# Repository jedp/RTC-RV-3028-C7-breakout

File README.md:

# RTC RV-3028-C7 Breakout Board

If you're using an Arduino, this goes nicely with Constantin Koch's
[RV-3038-C7-Arduino_Library](https://github.com/constiko/RV-3028_C7-Arduino_Library/),
which you can download direcly from the Arduino Library Manager.

Dimensions: 18.8mm x 22.6mm.

## BOM

- U1: RV-3028-C7 RTC
- C1: 0.1µ 0603
- C2: 0.1µ 0603
- R1: 10k 0603 (*Do Not Populate*; see datasheet for details.)
- R2: 10k 0603
- R3: 1k 0603
- R4: 10k 0603
- R5: 10k 0603
- R6: 10k 0603
- BT1: MS621F battery
- J1: Conn 1x4 female, 2.54mm
- J2: Conn 1x4 female, 2.54mm

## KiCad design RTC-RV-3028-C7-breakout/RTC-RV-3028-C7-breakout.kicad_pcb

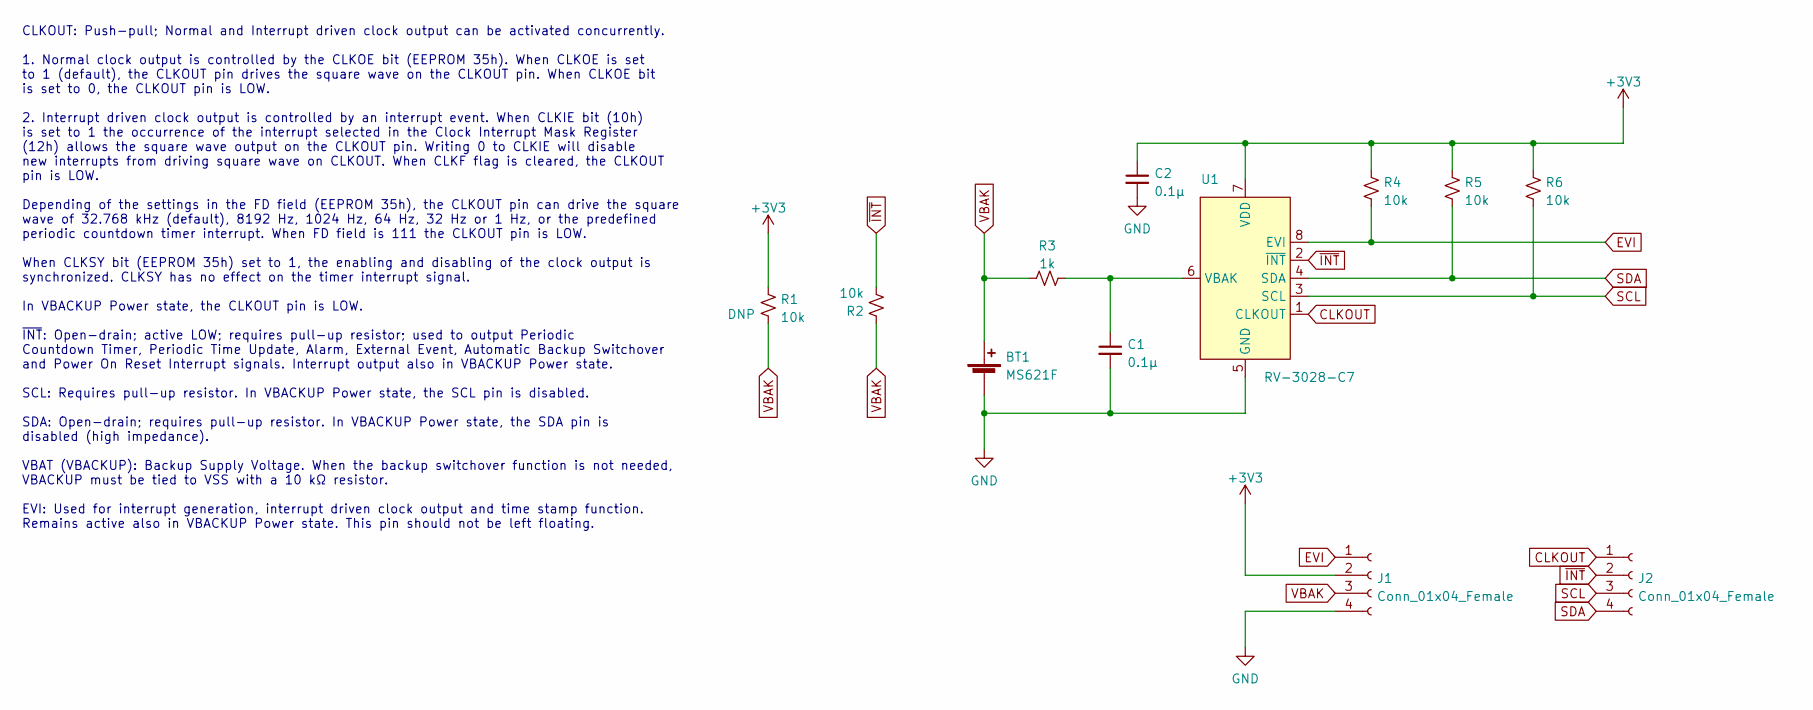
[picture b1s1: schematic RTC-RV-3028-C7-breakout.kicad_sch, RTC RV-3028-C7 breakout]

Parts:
BT1: MS621F; BatteryHolder_Seiko_MS621F
C1, C2: 0.1µ; C_0603_1608Metric
J1, J2: Conn_01x04_Female; PinSocket_1x04_P2.54mm_Vertical
R1, R2, R4, R5, R6: 10k; R_0603_1608Metric
R3: 1k; R_0603_1608Metric
U1: RV-3028-C7

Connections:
+3V3: C2.1, J1.2, R1.1, R4.1, R5.2, R6.2, U1.7 (VDD)
CLKOUT: J2.1, U1.1 (CLKOUT)
EVI: J1.1, R4.2, U1.8 (EVI)
GND: BT1.2 (-), C1.2, C2.2, J1.4, U1.5 (GND)
unnamed: C1.1, R3.2, U1.6 (VBAK)
SCL: J2.3, R6.1, U1.3 (SCL)
SDA: J2.4, R5.1, U1.4 (SDA)
VBAK: BT1.1 (+), J1.3, R1.2, R2.1, R3.1
~INT: J2.2, R2.2, U1.2 (~INT)

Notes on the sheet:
CLKOUT: Push-pull; Normal and Interrupt driven clock output can be activated concurrently. 1. Normal clock output is controlled by the CLKOE bit (EEPROM 35h). When CLKOE is set to 1 (default), the CLKOUT pin drives the square wave on the CLKOUT pin. When CLKOE bit is set to 0, the CLKOUT pin is LOW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

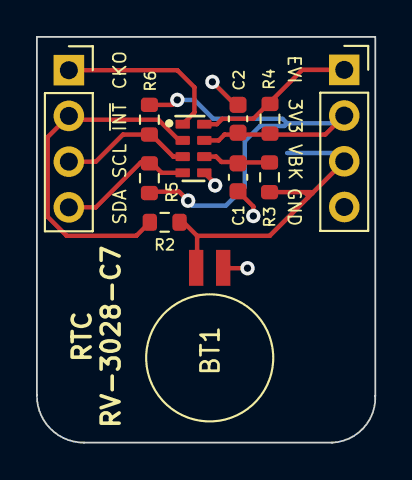
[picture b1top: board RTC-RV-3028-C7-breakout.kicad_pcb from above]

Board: 2 copper layers, 18.8 x 22.5 mm, 12 parts (1 on the bottom side), 9 nets.

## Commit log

2023-04-08 RV-3028-C7 breakout board
2023-04-08 Add bom
2023-04-14 Fix mis-labeled components
2023-04-21 Link to Arduino library
2023-04-21 Reminder not to populate R1
